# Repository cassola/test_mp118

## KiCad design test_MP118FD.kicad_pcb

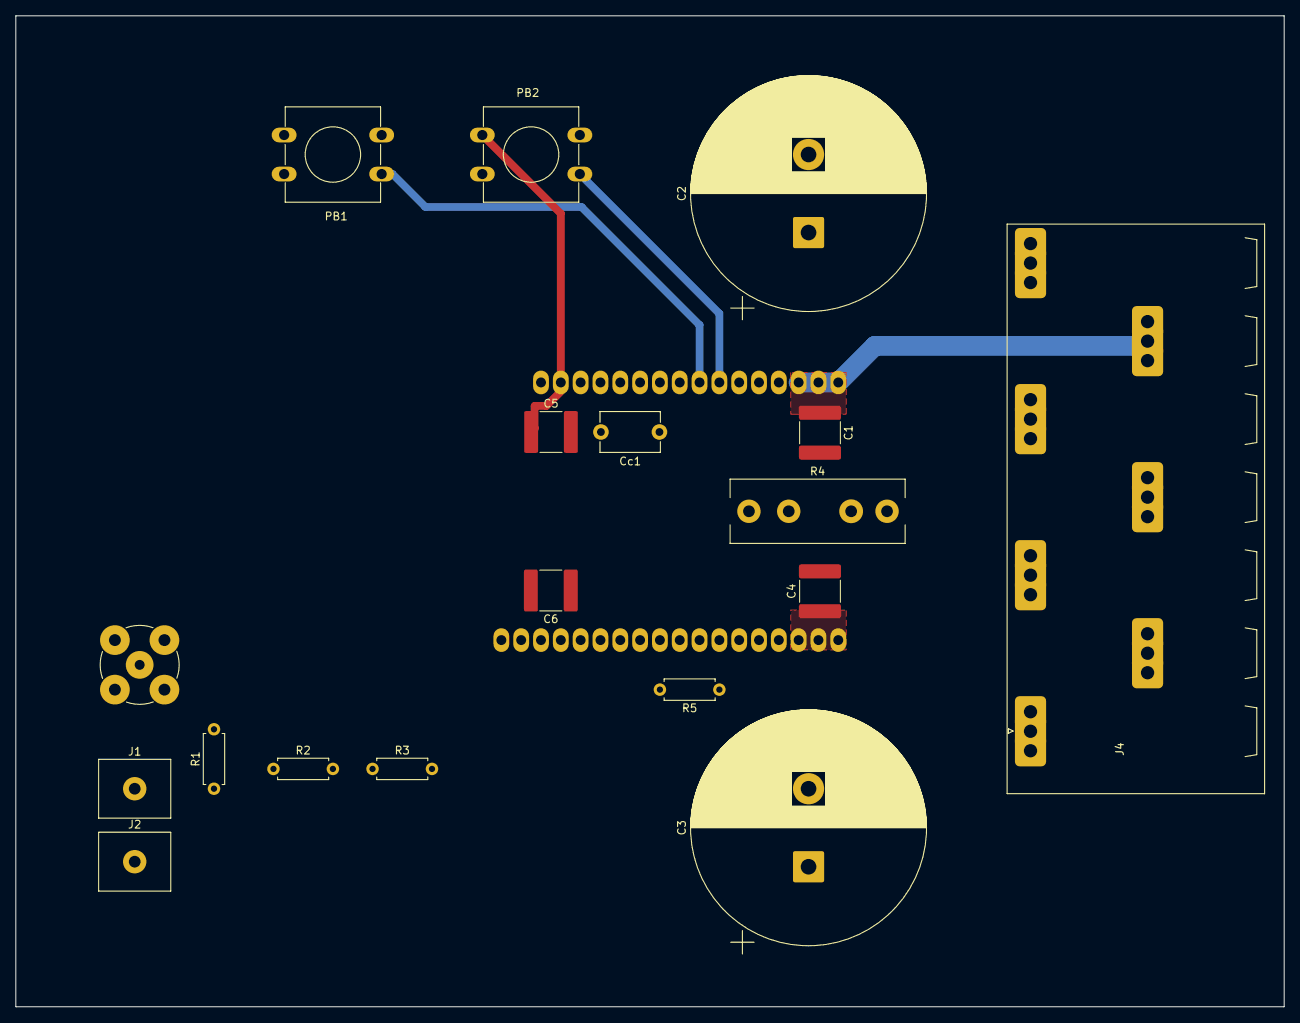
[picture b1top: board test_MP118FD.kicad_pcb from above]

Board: 2 copper layers, 162.6 x 127.0 mm, 19 parts (0 on the bottom side), 17 nets.

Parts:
C1, C4, C5, C6: 1uF; C_2220_5750Metric
C2, C3: 680uF; CP_Radial_D30.0mm_P10.00mm_SnapIn
Cc1: 10 pF; C_Disc_D7.5mm_W5.0mm_P7.50mm
J1, J2: Screw_Terminal_01x01; TerminalBlock_MetzConnect_360271_1x01_Horizontal_ScrewM3.0_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
J3: Conn_Coaxial; BNC_TEConnectivity_1478204_Vertical
J4: Conn_01x07_Socket; PhoenixContact_SPT_5_7-H-7.5-ZB_1x07_P7.5mm_Horizontal
PB1: SD; SW_PUSH-12mm
PB2: RESET; SW_PUSH-12mm
R1: 1K; R_Axial_DIN0207_L6.3mm_D2.5mm_P7.62mm_Horizontal
R2, R3: 10K; R_Axial_DIN0207_L6.3mm_D2.5mm_P7.62mm_Horizontal
R4: 0.54; Shunt PBV Isabellenhutte 17,78x7,62
R5: 0; R_Axial_DIN0207_L6.3mm_D2.5mm_P7.62mm_Horizontal
U MP118DF1: MP118

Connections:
/+Vb: C5.2, J4.3, U MP118DF1.4 (+Vb), U MP118DF1.8 (+Vb)
/+Vs: C1.1, C2.1, J4.2, U MP118DF1.14 (+Vs), U MP118DF1.15 (+Vs), U MP118DF1.16 (+Vs)
/-Vb: C6.1, J4.7, R5.2, U MP118DF1.25 (-Vb), U MP118DF1.30 (-Vb)
/-Vs: C3.1, C4.1, J4.6, R5.1, U MP118DF1.17 (-Vs), U MP118DF1.18 (-Vs), U MP118DF1.19 (-Vs)
/OUT: J4.4, R3.2, R4.4
/OUT_0: R4.1, U MP118DF1.11 (OUT), U MP118DF1.12 (OUT), U MP118DF1.13 (OUT), U MP118DF1.20 (OUT), U MP118DF1.21 (OUT), U MP118DF1.22 (OUT)
/SPARE: J4.1, U MP118DF1.7 (TEMP)
GND: C1.2, C2.2, C3.2, C4.2, C5.1, C6.2, J2.1, J3.2 (Ext), J4.5, PB1.4 (A), PB2.1, U MP118DF1.2 (BACK_PLT), U MP118DF1.3 (GND), U MP118DF1.32 (GND), U MP118DF1.33 (+IN)
unnamed: J1.1, J3.1 (In), R1.2
unnamed: PB2.4 (A), U MP118DF1.10 (RESET)
unnamed: R2.2, R3.1
unnamed: R4.2, U MP118DF1.28 (+Isd)
unnamed: R1.1, R2.1, U MP118DF1.34 (-IN)
unnamed: R4.3, U MP118DF1.27 (-Isd)
unnamed: Cc1.2, U MP118DF1.5 (Cc1)
unnamed: Cc1.1, U MP118DF1.6 (Cc2)
unnamed: PB1.1, U MP118DF1.9 (SD_)

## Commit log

2025-11-28 Primer commit
2025-11-28 confirmado
2025-11-28 borrador kicad_advanced
2025-11-28 condensadores
2025-11-28 con componentes
2025-11-28 con pdf
2025-11-30 Primer esquema, sin resistencias en serie, sin carga
2025-12-02 correccion pines mp118 y stp del co0nector phoenix 7p
2025-12-04 Reconfiguración general, arreglos de redes y posiciones mas centradas
2025-12-05 Hasta el viernes
